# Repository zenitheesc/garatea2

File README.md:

<h1 align="center" style="color:white; background-color:black">Garatéa 2</h1>
<h4 align="center">Our aerospace probes are attached to balloons filled with helium, carrying astrobiological experiments to the stratosphere, which is crucial so we can have a better understanding about how organisms can survive in space.</h4>

<p align="center">

</p>

<p align="center">
    <a href="#what-are-aerospace-probes">What are aerospace probes?</a> •
    <a href="#project">Project</a> •
    <a href="#details">Details</a> 
</p>

## What are aerospace probes?

 Our aerospace probes are balloons filled with helium, carrying astrobiological experiments to the stratosphere, which is crucial so we can have a better understanding about how organisms can survive in space.

Although they are part of a greater scientific experiment, the probes themselves are also fascinating from the point of view of embedded systems development. Our probes are equiped with microcontrolers, radios, sensors and cameras; every mission we aim to improve our systems so we can make the next mission even more efficient.

And, to sustain all our experiments and systems, we build reliable and reusable structures, that let us go to space multiple times. 

## Project

After Garatéa-1, our primary goal was to increase the quality of our Space Probes. The Embedded System Architecture was based on an Atmega. In software, we decide to pure C without the use of the Arduino functions, but we also permit the use of C++ during development. We also use Arduino Watchdog Timer. 

In our previous Space Probe, the sensors reads were not constant, because we didn't have solar panels. Now that we do, energy-saving was no longer an issue for us. So, we were able to make many reads. That was also our first try to use GitHub for code versioning. 

The structure was made with Kapton, Aeronautic Depron, 3D printing and Glass Fiber. 

## Details
| Launch Date |Max Altitude|Experiments|
|--|--|--|
| 19/12/2016 | 25,5 km |Bacteria Resistance testing & Biomolecules degradation pattern analysis|

| | | |
|:-------------------------:|:-------------------------:|:-------------------------:|
| |  ||
|  |  | |

---

<p align="center">

</p>
<p align = "center">
<a href="zenith.eesc@gmail.com">zenith.eesc@gmail.com</a>
</p>

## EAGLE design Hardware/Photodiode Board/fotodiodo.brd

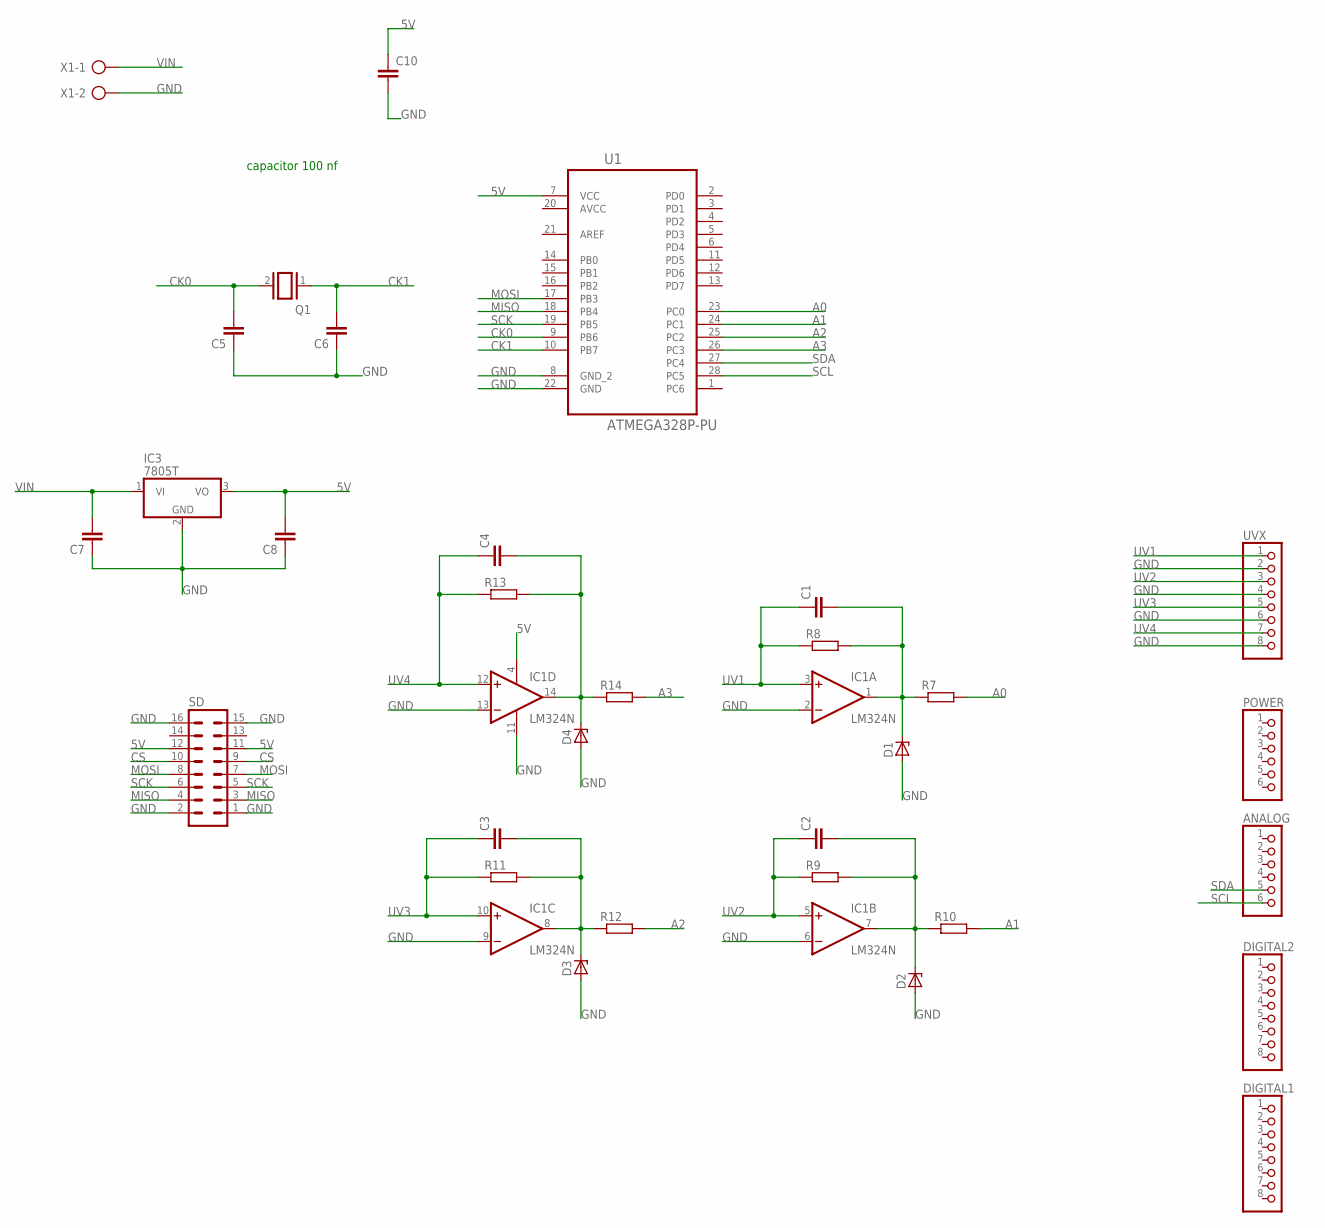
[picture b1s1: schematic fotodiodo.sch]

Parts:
ANALOG: PINHD-1X6; 1X06
C1, C2, C3, C4, C5, C6, C7, C8: C-EU025-025X050; C025-025X050
C10: C-EU050-055X075; C050-055X075
D1, D2, D3, D4: ZENER-DIODEC1702-15; C1702-15
DIGITAL1, DIGITAL2: PINHD-1X8; 1X08
IC1: LM324N; DIL14
IC3: 7805T; TO220H
POWER: PINHD-1X6; 1X06
Q1: XTAL/S; QS
R7, R8, R9, R10, R11, R12, R13, R14: R-EU_0207/10; 0207/10
SD: MA08-2
U1: ATMEGA328P-PU; DIP254P762X457-28
UVX: PINHD-1X8; 1X08
X1: AK500/2-H

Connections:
5V: C8.2, C10.1, IC1.4 (V+), IC3.3 (VO), SD.11, SD.12, U1.7 (VCC)
A0: R7.2, U1.23 (PC0)
A1: R10.2, U1.24 (PC1)
A2: R12.2, U1.25 (PC2)
A3: R14.2, U1.26 (PC3)
AVCC: U1.20 (AVCC)
CK0: C5.2, Q1.2, U1.9 (PB6)
CK1: C6.2, Q1.1, U1.10 (PB7)
CS: SD.9, SD.10
GND: C5.1, C6.1, C7.1, C8.1, C10.2, D1.A, D2.A, D3.A, D4.A, IC1.2 (-IN), IC1.6 (-IN), IC1.9 (-IN), IC1.11 (V-), IC1.13 (-IN), IC3.2 (GND), SD.1, SD.2, SD.15, SD.16, U1.8 (GND_2), U1.22 (GND), UVX.2, UVX.4, UVX.6, UVX.8, X1.2
MISO: SD.3, SD.4, U1.18 (PB4)
MOSI: SD.7, SD.8, U1.17 (PB3)
unnamed: C1.2, D1.C, IC1.1 (OUT), R7.1, R8.2
unnamed: C4.2, D4.C, IC1.14 (OUT), R13.2, R14.1
unnamed: C3.2, D3.C, IC1.8 (OUT), R11.2, R12.1
unnamed: C2.2, D2.C, IC1.7 (OUT), R9.2, R10.1
SCK: SD.5, SD.6, U1.19 (PB5)
SCL: ANALOG.6, U1.28 (PC5)
SDA: ANALOG.5, U1.27 (PC4)
UV1: C1.1, IC1.3 (+IN), R8.1, UVX.1
UV2: C2.1, IC1.5 (+IN), R9.1, UVX.3
UV3: C3.1, IC1.10 (+IN), R11.1, UVX.5
UV4: C4.1, IC1.12 (+IN), R13.1, UVX.7
VIN: C7.2, IC3.1 (VI), X1.1

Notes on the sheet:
capacitor 100 nf

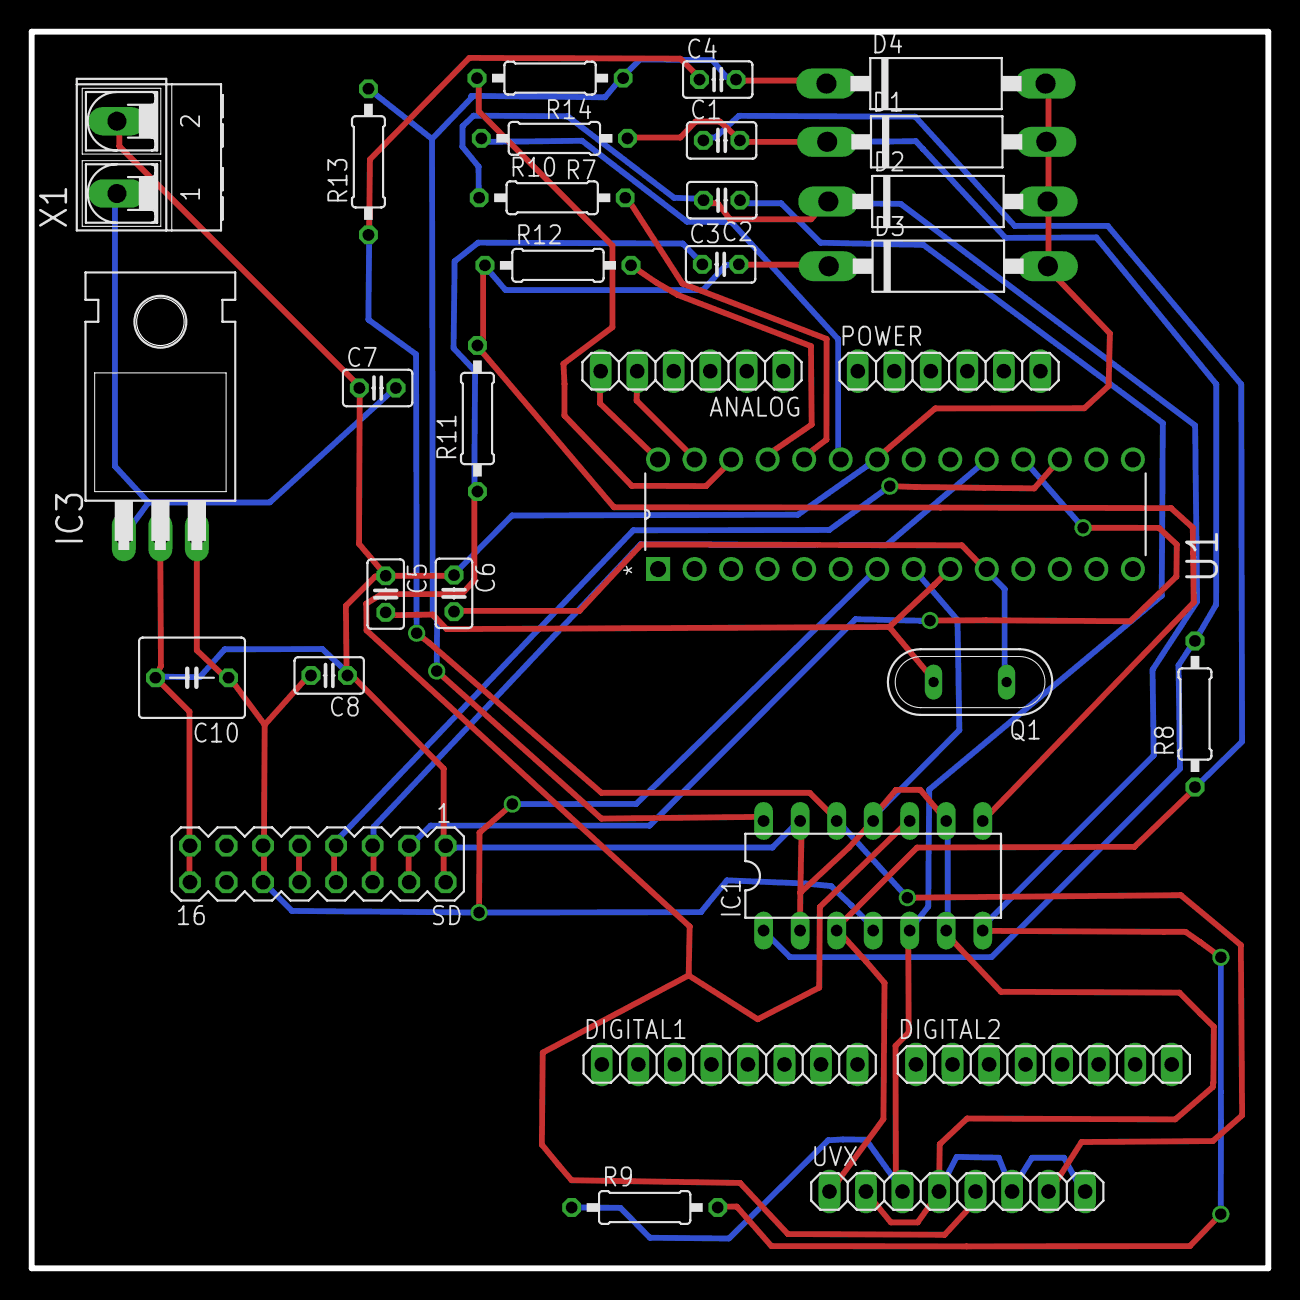
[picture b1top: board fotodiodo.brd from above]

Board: 2 copper layers, 86.0 x 86.0 mm, 32 parts (0 on the bottom side), 23 nets.

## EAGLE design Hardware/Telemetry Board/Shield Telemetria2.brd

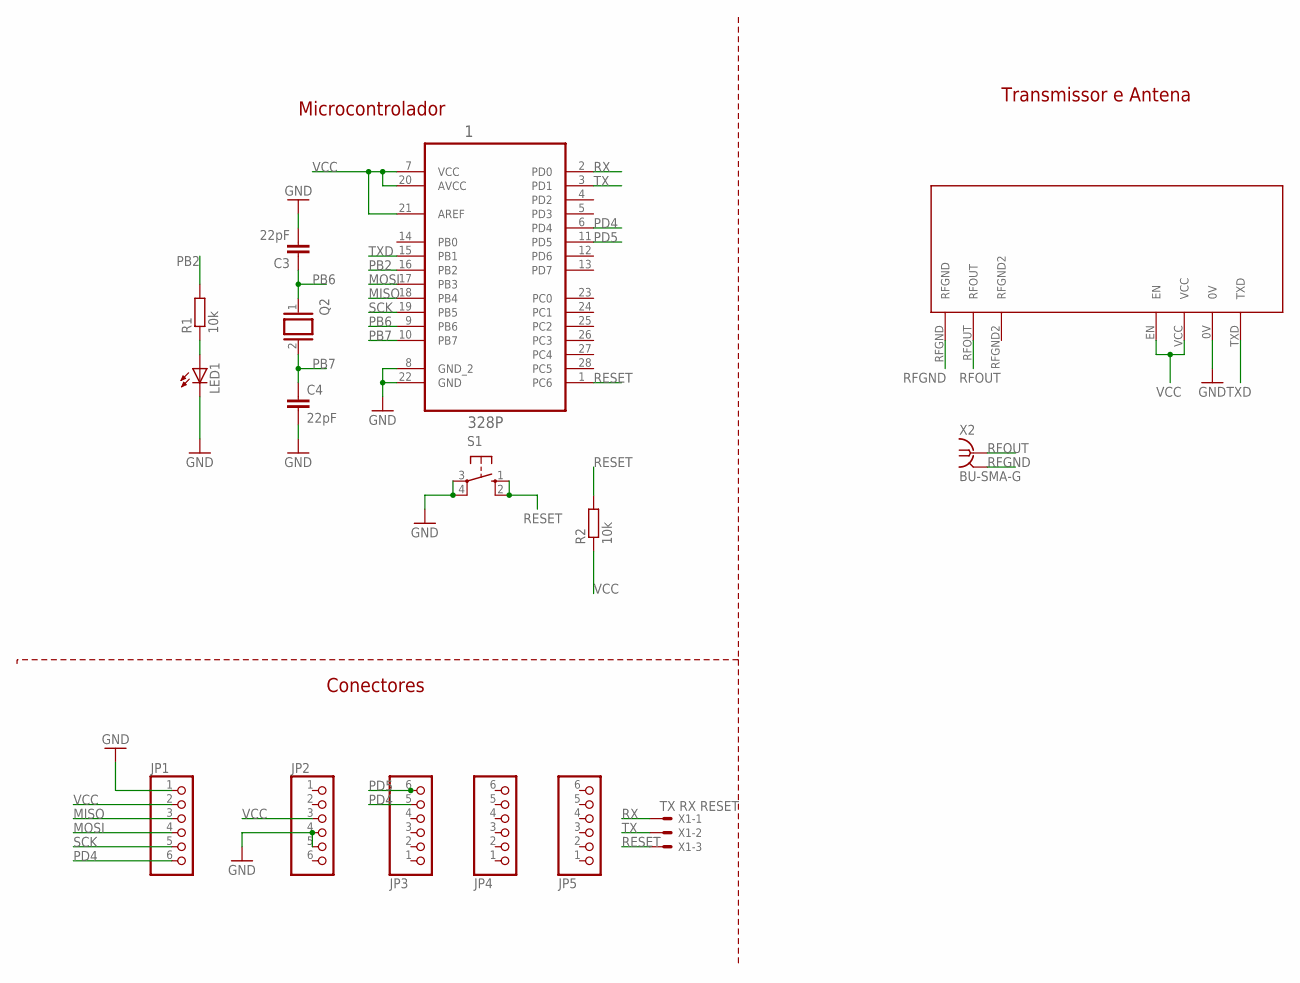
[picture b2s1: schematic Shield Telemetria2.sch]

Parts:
1: 328P; DIP254P762X457-28
C3, C4: 22pF; C5B4.5
JP1, JP2, JP3, JP4, JP5: PINHD-1X6; 1X06
LED1: LED3MM
Q2: XTAL/S; QS
R1, R2: 10k; 0207/10
S1: 10-XX; B3F-10XX
U$1: NTX2
X1: TX RX RESET; 22-23-2031
X2: BU-SMA-G

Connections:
GND: 1.8 (GND_2), 1.22 (GND), C3.2, C4.2, JP1.1, JP2.4, JP2.5, LED1.K (C), S1.3, S1.4 (P1), U$1.0V
MISO: 1.18 (PB4), JP1.3
MOSI: 1.17 (PB3), JP1.4
unnamed: LED1.A, R1.1
PB2: 1.16 (PB2), R1.2
PB6: 1.9 (PB6), C3.1, Q2.1
PB7: 1.10 (PB7), C4.1, Q2.2
PD4: 1.6 (PD4), JP1.6, JP3.5
PD5: 1.11 (PD5), JP3.6
RESET: 1.1 (PC6), R2.2, S1.1 (S), S1.2 (S1), X1.3
RFGND: U$1.RFGND, X2.2, X2.3 (2), X2.4 (2), X2.5 (2)
RFOUT: U$1.RFOUT, X2.1
RX: 1.2 (PD0), X1.1
SCK: 1.19 (PB5), JP1.5
TX: 1.3 (PD1), X1.2
TXD: 1.15 (PB1), U$1.TXD
VCC: 1.7 (VCC), 1.20 (AVCC), 1.21 (AREF), JP1.2, JP2.3, R2.1, U$1.EN, U$1.VCC

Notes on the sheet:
Conectores
Microcontrolador
Transmissor e Antena

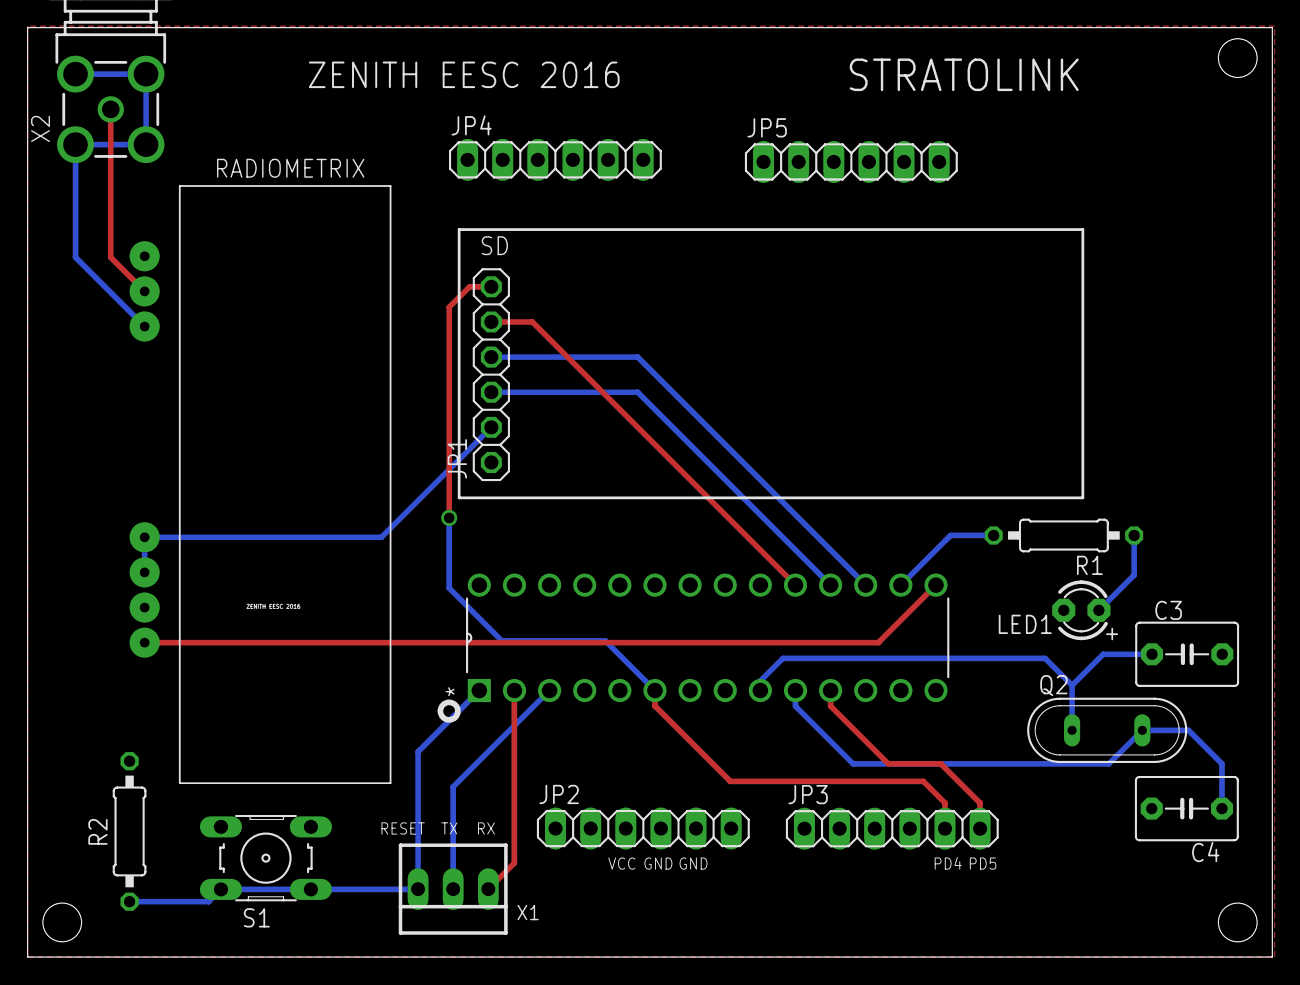
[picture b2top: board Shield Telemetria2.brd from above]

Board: 2 copper layers, 90.0 x 67.2 mm, 16 parts (0 on the bottom side), 17 nets.

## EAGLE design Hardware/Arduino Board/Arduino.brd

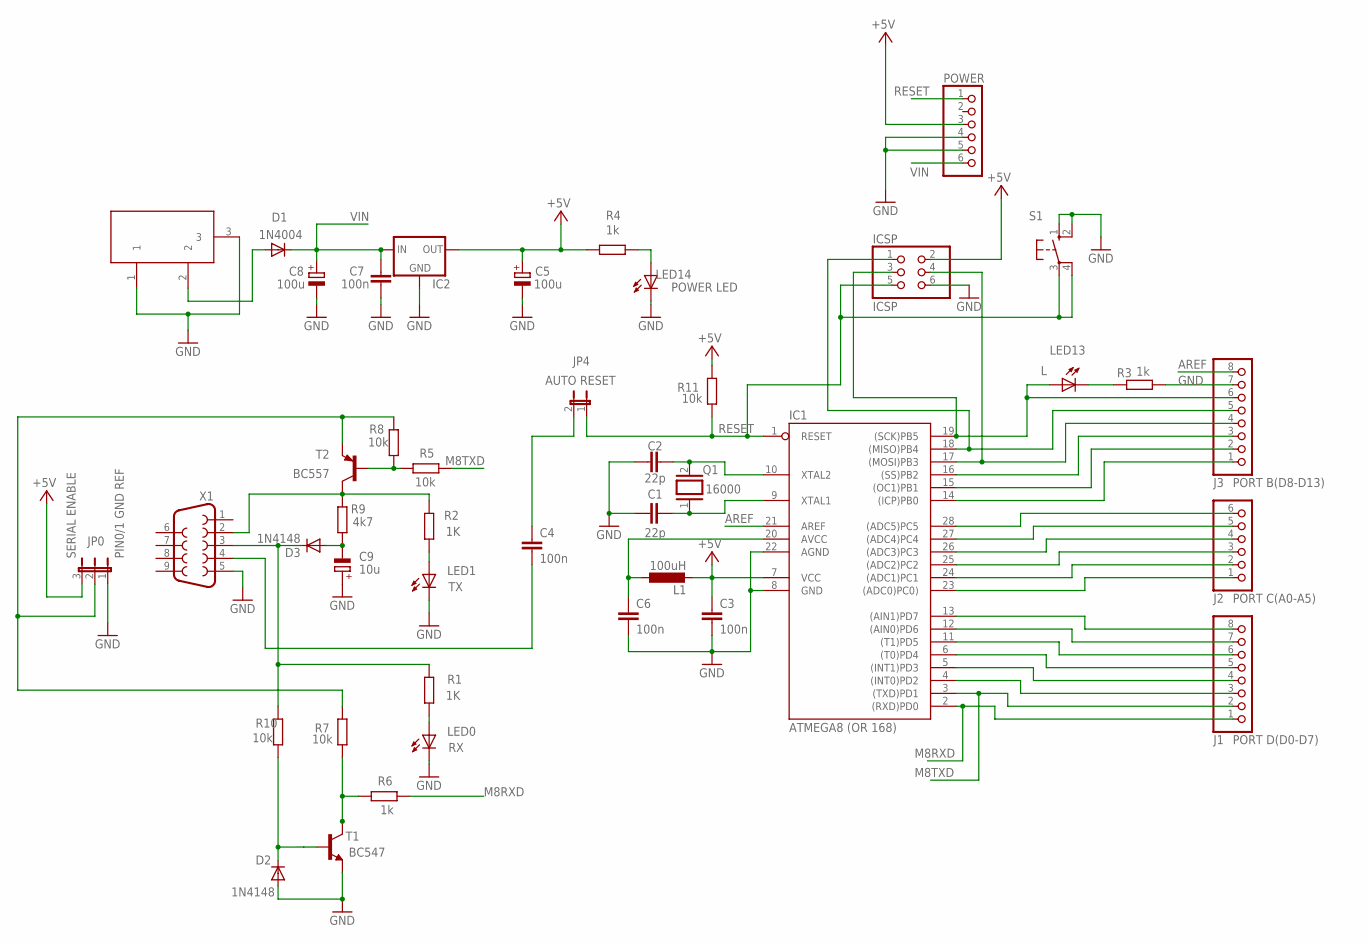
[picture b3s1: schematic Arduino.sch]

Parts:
C1, C2: 22p; C050-025X075
C3, C4, C6, C7: 100n; C050-025X075
C5, C8: 100u; E3,5-8
C9: 10u; E5-6
D1: 1N4004; DO41-10
D2, D3: 1N4148; DO35-10
DC1: DC21MMX; DC-21MM
IC1: ATMEGA8 (OR 168); DIL28-3
IC2: 78XXL
ICSP: ICSP; 2X03
J1: PORT D(D0-D7); 1X08
J2: PORT C(A0-A5); 1X06
J3: PORT B(D8-D13); 1X08
JP0: JP2W
JP4: AUTO RESET; JP1W
L1: 100uH; 0207/10
LED0: RX; LED3MM
LED1: TX; LED3MM
LED13: L; LED3MM
LED14: POWER LED; LED3MM
POWER: PINHD-1X6; 1X06
Q1: 16000; Q
R1, R2: 1K; 0207/10
R3, R4, R6: 1k; 0207/10
R5, R7, R8, R10, R11: 10k; 0207/10
R9: 4k7; 0207/10
S1: 10-XX; B3F-10XX
T1: BC547; TO92
T2: BC557; TO92-EBC
X1: F09H

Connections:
+5V: C3.1, C5.+, IC1.7 (VCC), IC2.OUT, ICSP.2, JP0.3, L1.2, POWER.3, R4.2, R11.2
AREF: IC1.21 (AREF), J3.8
GND: C1.1, C2.1, C3.2, C5.-, C6.2, C7.1, C8.-, C9.+, D2.A, DC1.1, DC1.3, IC1.8 (GND), IC1.22 (AGND), IC2.GND, ICSP.6, J3.7, JP0.1, LED0.K (C), LED1.K (C), LED14.K (C), POWER.4, POWER.5, R3.1, S1.1 (S), S1.2 (S1), T1.1 (E), X1.5
M8RXD: IC1.2 ((RXD)PD0), J1.1, R6.1
M8TXD: IC1.3 ((TXD)PD1), J1.2, R5.1
unnamed: IC1.18 ((MISO)PB4), ICSP.1, J3.5
unnamed: C9.-, D3.A, R9.1
unnamed: LED14.A, R4.1
unnamed: IC1.17 ((MOSI)PB3), ICSP.4, J3.4
unnamed: IC1.14 ((ICP)PB0), J3.1
unnamed: C1.2, IC1.9 (XTAL1), Q1.1
unnamed: C2.2, IC1.10 (XTAL2), Q1.2
unnamed: D1.A, DC1.2
unnamed: IC1.4 ((INT0)PD2), J1.3
unnamed: IC1.5 ((INT1)PD3), J1.4
unnamed: IC1.6 ((T0)PD4), J1.5
unnamed: IC1.11 ((T1)PD5), J1.6
unnamed: IC1.12 ((AIN0)PD6), J1.7
unnamed: IC1.13 ((AIN1)PD7), J1.8
unnamed: IC1.23 ((ADC0)PC0)), J2.1
unnamed: IC1.24 ((ADC1)PC1), J2.2
unnamed: IC1.25 ((ADC2)PC2), J2.3
unnamed: IC1.26 ((ADC3)PC3), J2.4
unnamed: IC1.27 ((ADC4)PC4), J2.5
unnamed: IC1.28 ((ADC5)PC5), J2.6
unnamed: IC1.15 ((OC1)PB1), J3.2
unnamed: IC1.16 ((SS)PB2), J3.3
unnamed: D3.C, R1.2, R10.2, X1.3
unnamed: R6.2, R7.1, T1.3 (C)
unnamed: R5.2, R8.2, T2.B
unnamed: D2.C, R10.1, T1.2 (B)
unnamed: LED13.K (C), R3.2
unnamed: LED1.A, R2.1
unnamed: LED0.A, R1.1
unnamed: C4.1, JP4.2
unnamed: C4.2, X1.4
unnamed: R2.2, R9.2, T2.C, X1.2
unnamed: C6.1, IC1.20 (AVCC), L1.1
RESET: IC1.1 (RESET), ICSP.5, JP4.1, POWER.1, R11.1, S1.3, S1.4 (P1)
SCK: IC1.19 ((SCK)PB5), ICSP.3, J3.6, LED13.A
SERIAL_VCC: JP0.2, R7.2, R8.1, T2.E
VIN: C7.2, C8.+, D1.C, IC2.IN, POWER.6

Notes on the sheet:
PIN0/1 GND REF
SERIAL ENABLE

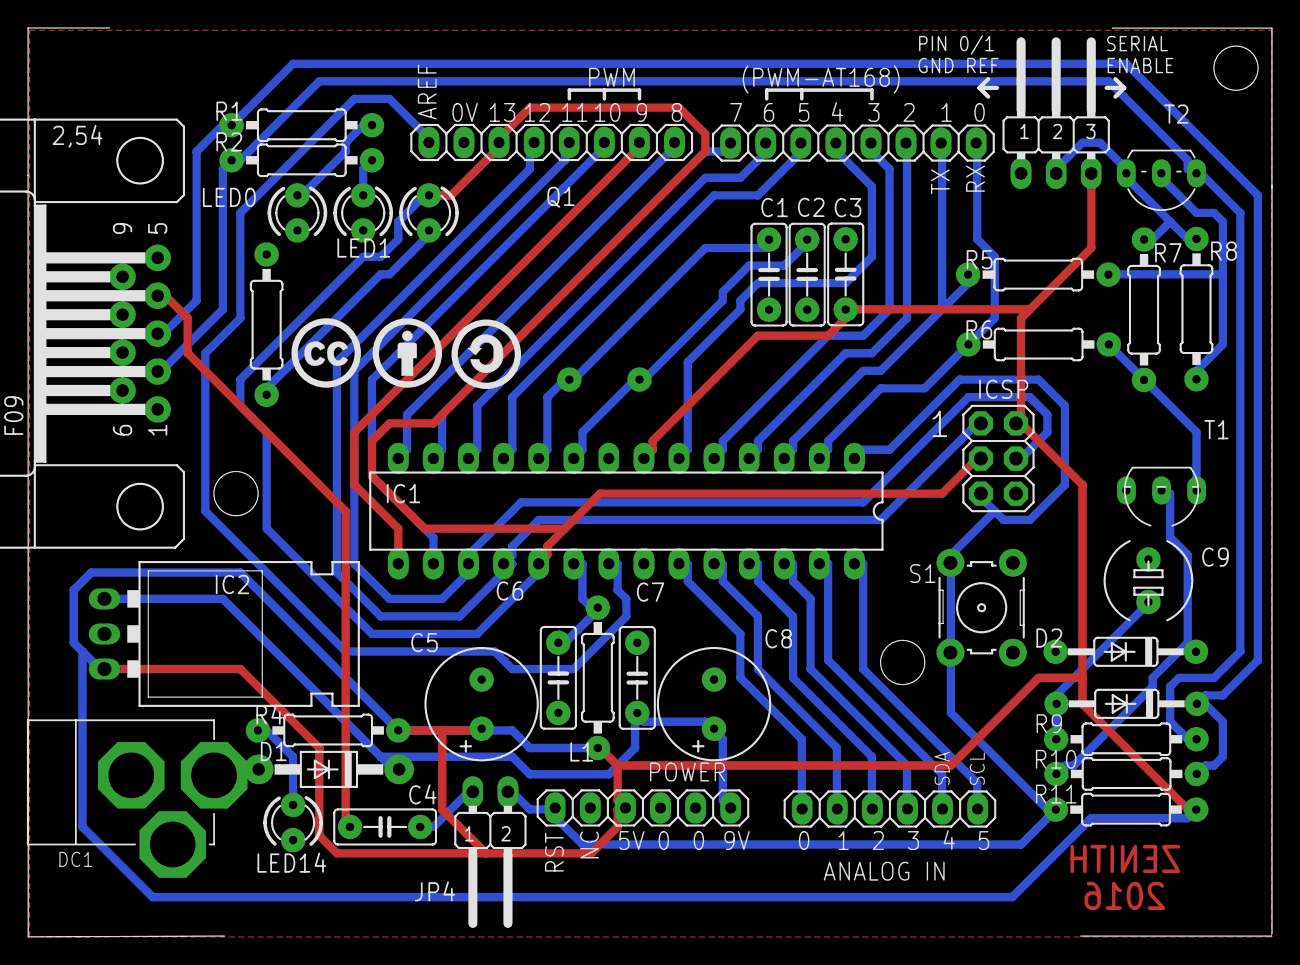
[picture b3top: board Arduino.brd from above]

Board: 2 copper layers, 90.1 x 65.8 mm, 46 parts (1 on the bottom side), 42 nets.

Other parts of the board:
U$1: CC
U$2: BY
U$3: SA

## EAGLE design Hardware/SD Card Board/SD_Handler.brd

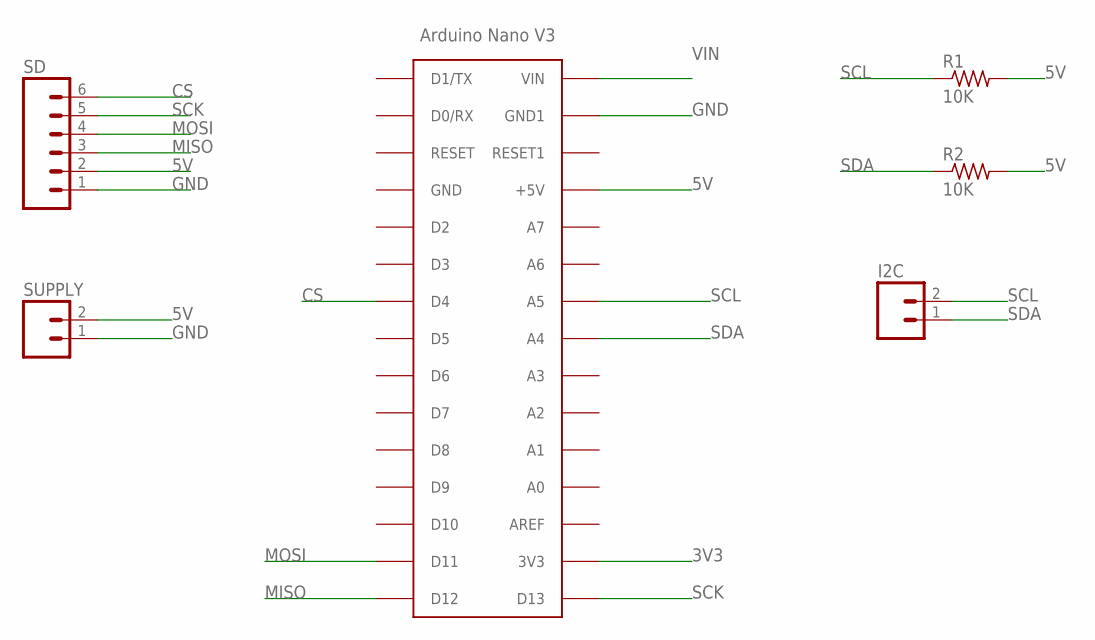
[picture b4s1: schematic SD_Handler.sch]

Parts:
I2C: M02; 02P
R1, R2: 10K; 0207/10
SD: M06LONGPADS; 1X06_LONGPADS
SUPPLY: M02; 02P
U$1: ARDUINONANO; PDIP-32

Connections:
3V3: U$1.3V3
5V: R1.2, R2.2, SD.2, SUPPLY.2, U$1.+5V
CS: SD.6, U$1.D4
GND: SD.1, SUPPLY.1, U$1.GND1
MISO: SD.3, U$1.D12
MOSI: SD.4, U$1.D11
SCK: SD.5, U$1.D13
SCL: I2C.2, R1.1, U$1.A2 (A5)
SDA: I2C.1, R2.1, U$1.A3 (A4)
VIN: U$1.VIN

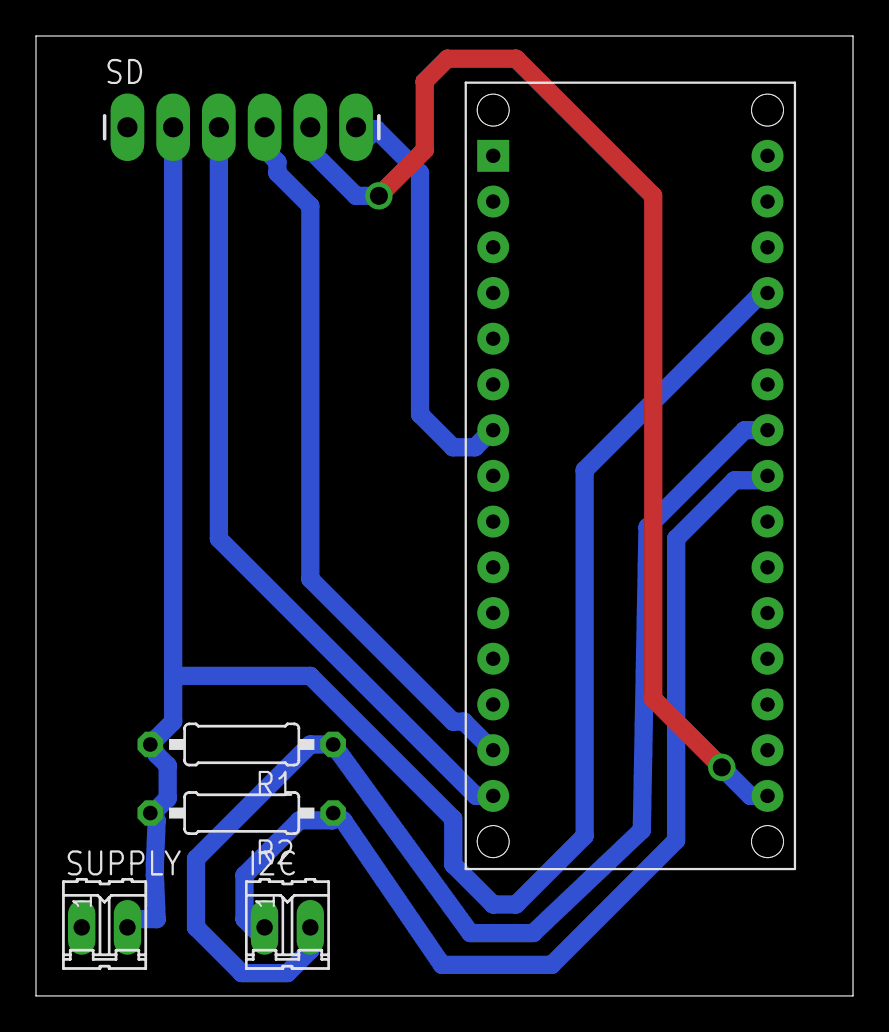
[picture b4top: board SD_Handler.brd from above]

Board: 2 copper layers, 45.4 x 53.3 mm, 6 parts (0 on the bottom side), 8 nets.

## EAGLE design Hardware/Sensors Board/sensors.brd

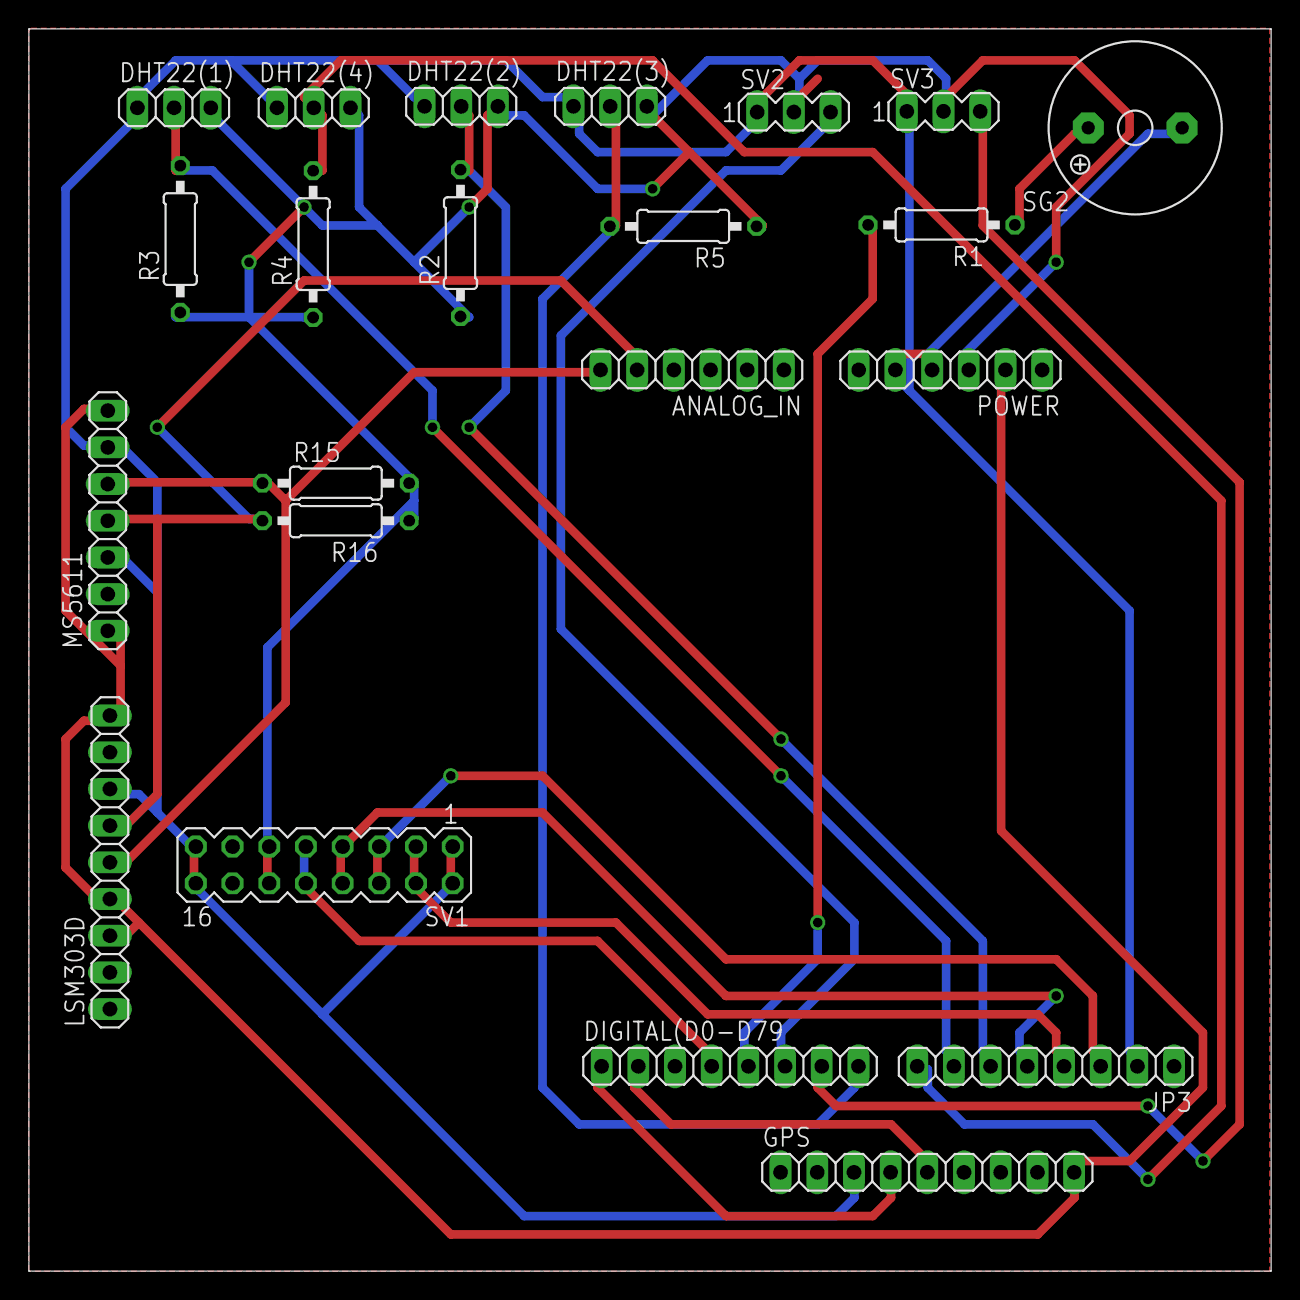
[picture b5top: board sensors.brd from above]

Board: 2 copper layers, 86.0 x 86.0 mm, 22 parts (0 on the bottom side), 19 nets.

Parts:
ANALOG_IN: 1X06
DHT22(1), DHT22(2), DHT22(3), DHT22(4): 1X03
DIGITAL(D0-D79: 1X08
GPS: 1X09
JP3: 1X08
LSM303D: 1X09
MS5611: 1X07
POWER: 1X06
R1, R2, R3, R4, R5, R15, R16: 0207/10
SG2: F/QMBIII
SV1: MA08-2
SV2, SV3: MA03-1

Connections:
3.3V: GPS.9, LSM303D.3, LSM303D.4, LSM303D.9, MS5611.1, MS5611.7, POWER.2
5: DIGITAL(D0-D79.6, SV2.3
5V: DHT22(1).3, DHT22(2).3, DHT22(3).3, DHT22(4).3, POWER.3, R2.1, R3.1, R4.1, R5.1, R15.2, R16.1, SV1.11, SV1.12, SV2.2, SV3.2
6: DIGITAL(D0-D79.7, SV3.3
7: DHT22(3).2, DIGITAL(D0-D79.8, R5.2
8: DHT22(4).2, JP3.8, R4.2
9: DHT22(1).2, JP3.7, R3.2
10: DHT22(2).2, JP3.6, R2.2
BUZZER: DIGITAL(D0-D79.5, R1.2
CS: DIGITAL(D0-D79.4, SV1.9, SV1.10
GND: DHT22(1).1, DHT22(2).1, DHT22(3).1, DHT22(4).1, GPS.3, JP3.2, LSM303D.7, MS5611.3, MS5611.6, POWER.4, POWER.5, SG2.-, SV1.1, SV1.2, SV1.15, SV1.16, SV2.1, SV3.1
MISO: JP3.4, SV1.3, SV1.4
MOSI: JP3.5, SV1.7, SV1.8
unnamed: R1.1, SG2.+
RX: DIGITAL(D0-D79.1, GPS.4
SCK: JP3.3, SV1.5, SV1.6
SCL: ANALOG_IN.6, LSM303D.5, MS5611.5, R15.1
SDA: ANALOG_IN.5, LSM303D.6, MS5611.4, R16.2
TX: DIGITAL(D0-D79.2, GPS.5

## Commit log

2016-10-05 Initial commit with humidity sensor.
2016-10-12 Interface Orientada a Objeto para o Buzzer... Metodos ainda nao implementados
2016-10-12 Interface Orientada a Objeto para o Buzzer... Metodos ainda nao implementados atualizado
2016-10-13 a
    a
2016-10-17 Classes do BUZZER finalizadas e compilando.
2016-10-28 Biblioteca para servo compilando.
2016-11-04 Create stratolink
2016-11-04 subida/descida/chão
    funções da g1 que identificam subida descida e queda, através de mins
    qds
2016-11-09 Biblioteca DS18B20 orientada compilando
2016-11-10 Biblioteca do Acelerômetro com Herança
    Compilando e testada com .ino incluído.
2016-11-10 Tudo, por equanto.
    :)
2016-11-10 att da tudo
2016-11-10 tudo ok na onboard
2016-11-10 nada a declarar
2016-11-10 hGPS semi funcional
2016-11-11 Estamos sempre trabalhando para lhe proporcionar uma melhor experiencia.
2016-11-14 Compilando e entrando na Climbing mode + serial funcionando
2016-11-16 Todos os sesores funcionando menos GPS e acelerometro - Pinagem duvidosa.
2016-11-16 algumas melhorias
2016-11-17 na on
2016-11-17 gps + sd
2016-11-18 Atualizada tentando economizar espaco
2016-11-18 NOVAS FUNÇOES NA STATE MACH
2016-11-18 Tudo compilando
    98% da memória RAM utilizada.
2016-11-18 Adicionado o macro F() nas strings
2016-11-18 hSD com fatSD
    compilando 99%.....
2016-11-18 alguns ajustes.....
2016-11-18 testando i2c
2016-11-23 final 1.0
2016-12-14 Pequenas alterações
2018-03-15 Code compiling rev1
2018-03-19 TinyGPS and GPS objects updated (Compiling)
    hGPS is no longer used. SoftwareSerial and TinyGPS added.
2021-04-17 Update README.md
    fixed links
2021-04-17 Assets: added images
2021-04-17 Readme: added image grid
2021-04-18 organizing the repo and adding files
2021-04-18 adding one more picture to the grid
2021-04-18 adding one more picture to the README
2021-04-18 adding the topic for project

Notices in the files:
parts and their libraries:
SparkFun: Licensing: Creative Commons ShareAlike 4.0 International - https://creativecommons.org/licenses/by-sa/4.0
